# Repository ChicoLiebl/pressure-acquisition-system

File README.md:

# pressure-acquisition-system

Acquisition system for a piezoelectric pressure sensor, model 601A from Kistler. This system was developed as my electrical engineering graduation project.

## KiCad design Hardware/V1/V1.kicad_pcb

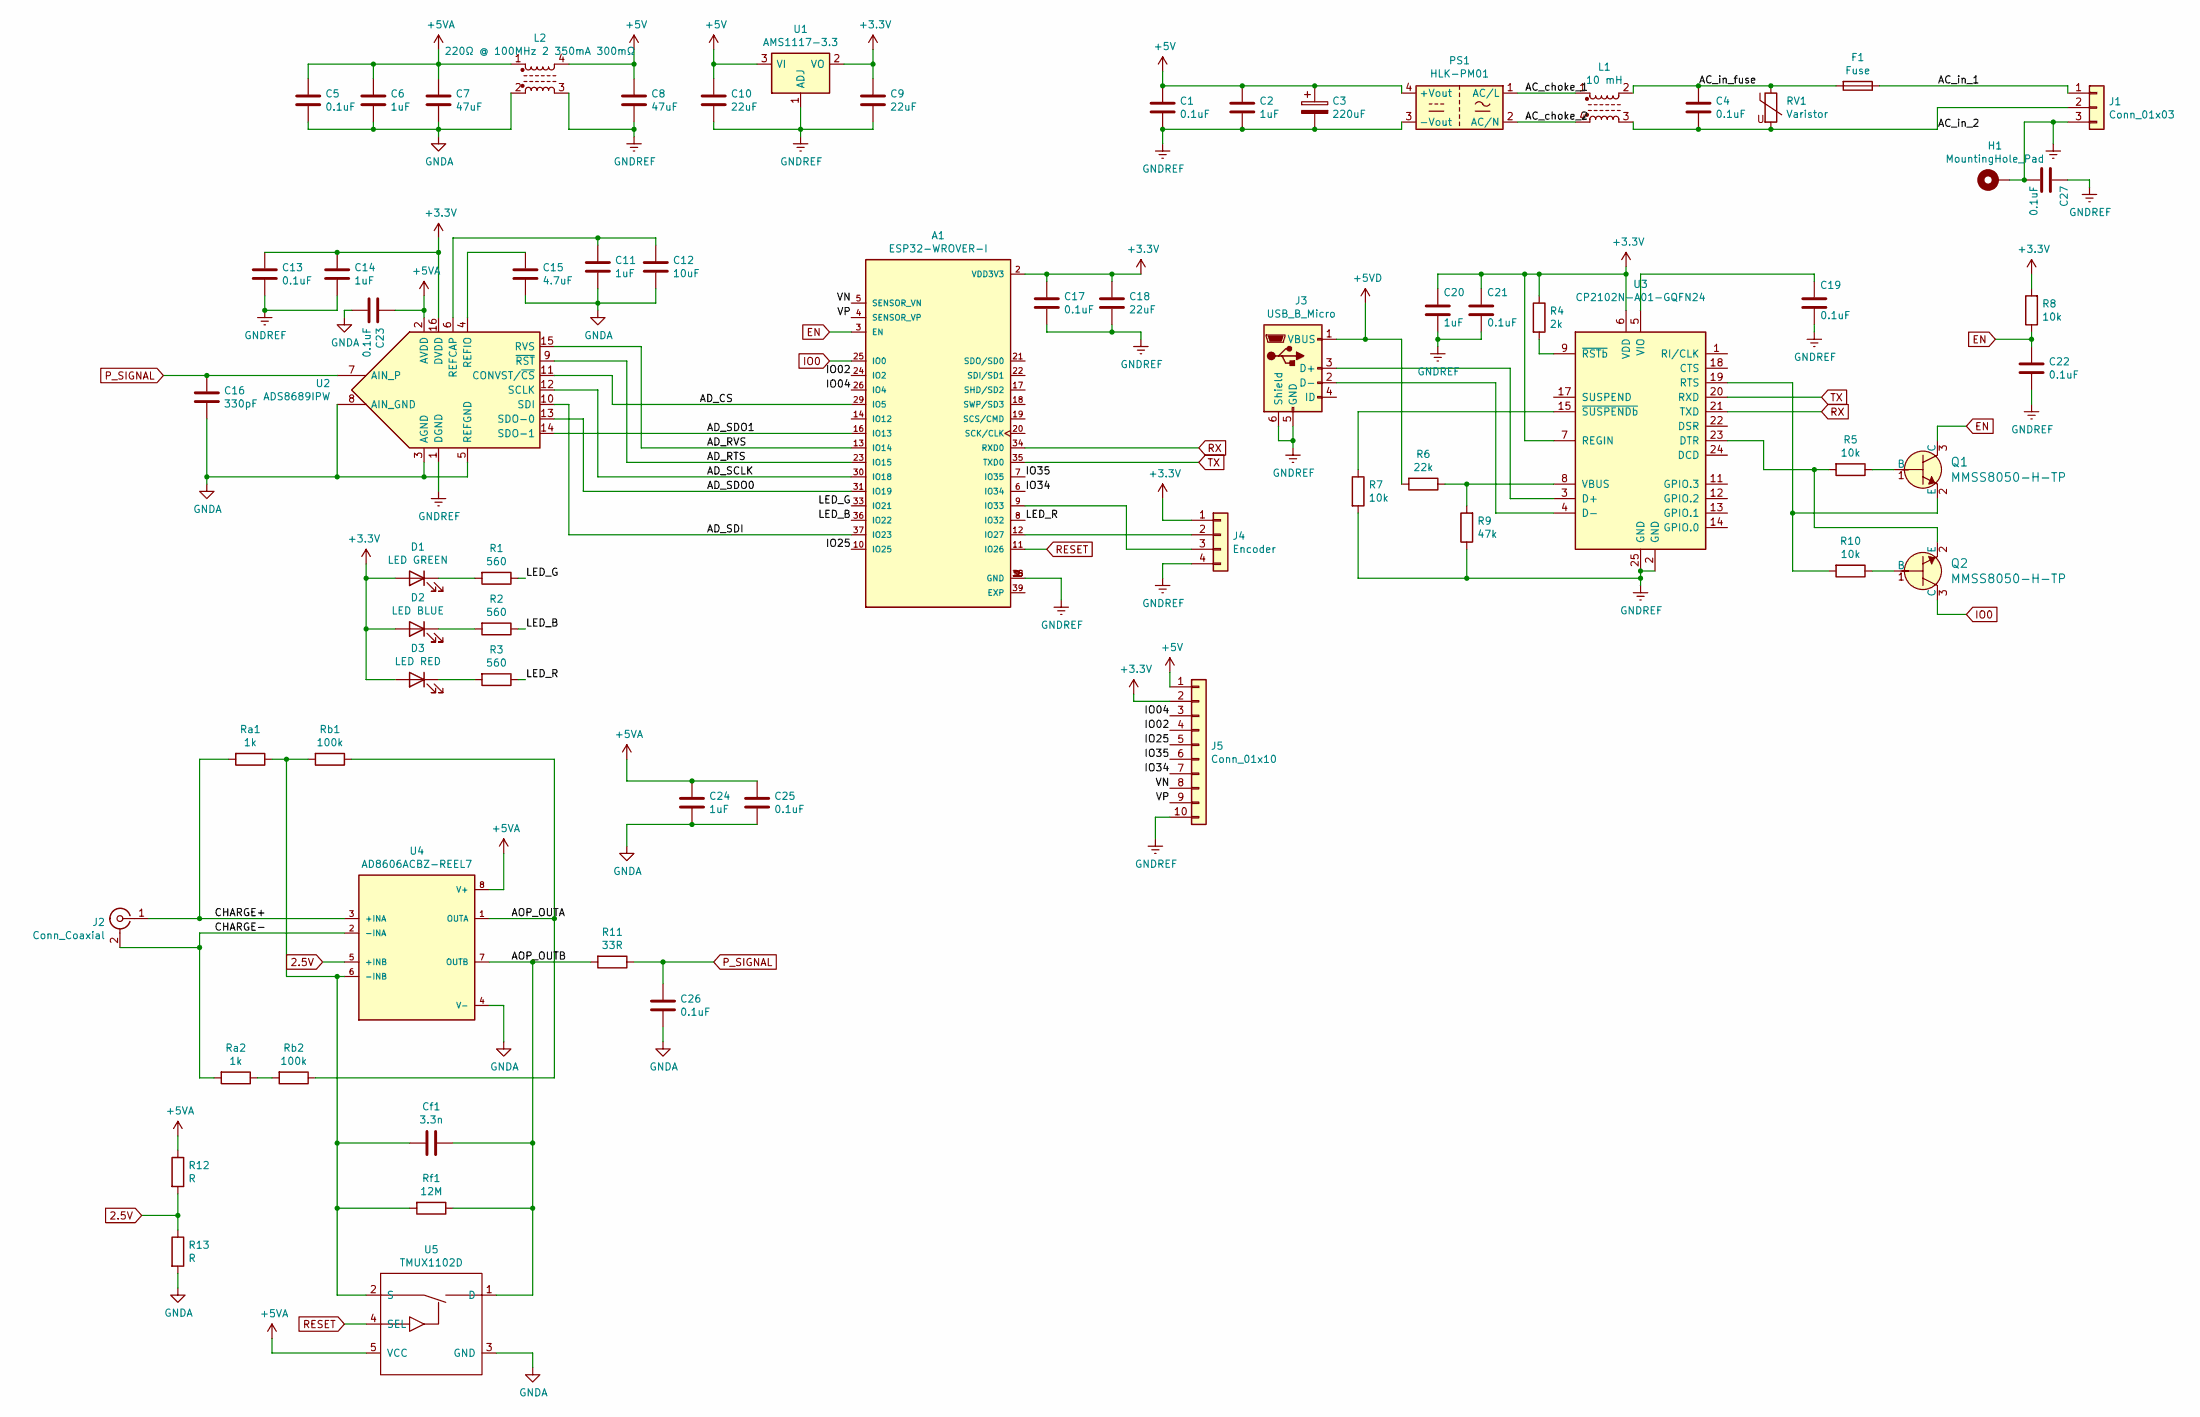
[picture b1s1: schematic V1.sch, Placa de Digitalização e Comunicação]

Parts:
A1: ESP32-WROVER-I; XCVR_ESP32-WROVER-I; DIGI-KEY_PART_NUMBER 1904-1008-1-ND
C1, C5, C13, C17, C19, C21, C22, C23, C25, C26, C27: 0.1uF; 0603
C2, C6, C11, C14, C20, C24: 1uF; 0805
C3: 220uF; CP_Radial_D10.0mm_P2.50mm
C4: 0.1uF; C_Rect_L9.0mm_W3.8mm_P7.50mm_MKT
C7, C8: 47uF; 1206
C9, C10, C18: 22uF; 0805
C12: 10uF; 0805
C15: 4.7uF; 0805
C16: 330pF; 0603
Cf1: 3.3n; 0603
D1: LED GREEN; 0603
D2: LED BLUE; 0603
D3: LED RED; 0603
F1: Fuse; Fuse_BelFuse_0ZRE0025FF_L9.6mm_W3.8mm
H1: MountingHole_Pad; MountingHole_2.2mm_M2_DIN965_Pad
J1: Conn_01x03; AC-Input
J2: Conn_Coaxial; BNC_Header
J3: USB_B_Micro; USB_Micro-AB_Molex_47590-0001
J4: Encoder; PinHeader_1x04_P1.27mm_Vertical
J5: Conn_01x10; PinHeader_1x10_P2.54mm_Vertical
L1: 10 mH; UU9.8
L2: 220Ω @ 100MHz 2 350mA 300mΩ; ACM3225-2P
PS1: HLK-PM01; Converter_ACDC_HiLink_HLK-PMxx
Q1, Q2: MMSS8050-H-TP; SOT-23-3; MPN MMSS8050-H-TP; Digi-Key_PN MMSS8050-H-TPMSCT-ND
R1, R2, R3: 560; 0603
R4: 2k; 0603
R5, R7, R8, R10: 10k; 0603
R6: 22k; 0603
R9: 47k; 0603
R11: 33R; 0603
R12, R13: R; 0603
RV1: Varistor; RV_Disc_D12mm_W3.9mm_P7.5mm
Ra1, Ra2: 1k; 0603
Rb1, Rb2: 100k; 0603
Rf1: 12M; 0603
U1: AMS1117-3.3; SOT-223-3_TabPin2
U2: ADS8689IPW; TSSOP-16_4.4x5mm_P0.65mm
U3: CP2102N-A01-GQFN24; QFN-24-1EP_4x4mm_P0.5mm_EP2.6x2.6mm
U4: AD8606ACBZ-REEL7; SOIC-8_3.9x4.9mm_P1.27mm; PARTREV O
U5: TMUX1102D; SOT-23-5_HandSoldering

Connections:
2.5V: R12.2, R13.1, U4.5 (+INB)
+3V3: A1.2 (VDD3V3), C9.1, C13.1, C14.1, C17.1, C18.1, C20.1, C21.1, D1.2 (A), D2.2 (A), D3.2 (A), J4.1, J5.2, R4.1, R8.2, U1.2 (VO), U2.16 (DVDD), U3.6 (VDD), U3.7 (REGIN)
+5V: C1.1, C2.1, C3.1, C8.1, C10.1, J5.1, L2.4, PS1.4 (+Vout), U1.3 (VI)
+5VA: C5.1, C6.1, C7.1, C23.1, C24.1, C25.1, L2.1, R12.1, U2.2 (AVDD), U4.8 (V+), U5.5 (VCC)
+5VD: J3.1 (VBUS), R6.2
/AC_choke_1: L1.1, PS1.1 (AC/L)
/AC_choke_2: L1.4, PS1.2 (AC/N)
/AC_in_1: F1.1, J1.1
/AC_in_2: C4.2, J1.2, L1.3, RV1.2
/AC_in_fuse: C4.1, F1.2, L1.2, RV1.1
/AD_CS: A1.29 (IO5), U2.11 (CONVST/~CS)
/AD_RTS: A1.23 (IO15), U2.9 (~RST)
/AD_RVS: A1.13 (IO14), U2.15 (RVS)
/AD_SCLK: A1.30 (IO18), U2.12 (SCLK)
/AD_SDI: A1.37 (IO23), U2.10 (SDI)
/AD_SDO0: A1.31 (IO19), U2.13 (SDO-0)
/AD_SDO1: A1.16 (IO13), U2.14 (SDO-1)
/AOP_OUTA: Rb1.1, Rb2.1, U4.1 (OUTA)
/AOP_OUTB: Cf1.1, R11.2, Rf1.1, U4.7 (OUTB), U5.1 (D)
/CHARGE+: J2.1 (In), Ra1.2, U4.3 (+INA)
/CHARGE-: J2.2 (Ext), Ra2.2, U4.2 (-INA)
/IO02: A1.24 (IO2), J5.4
/IO04: A1.26 (IO4), J5.3
/IO25: A1.10 (IO25), J5.5
/IO34: A1.6 (IO34), J5.7
/IO35: A1.7 (IO35), J5.6
/LED_B: A1.36 (IO22), R2.1
/LED_G: A1.33 (IO21), R1.1
/LED_R: A1.8 (IO32), R3.1
/VN: A1.5 (SENSOR_VN), J5.8
/VP: A1.4 (SENSOR_VP), J5.9
EN: A1.3 (EN), C22.1, Q1.3 (C), R8.1
Earth: C27.2, H1.1, J1.3
GNDA: C5.2, C6.2, C7.2, C11.2, C12.2, C15.2, C16.2, C23.2, C24.2, C25.2, C26.2, L2.2, R13.2, U2.3 (AGND), U2.5 (REFGND), U2.8 (AIN_GND), U4.4 (V-), U5.3 (GND)
GNDREF: A1.1 (GND), A1.15 (GND), A1.38 (GND), C1.2, C2.2, C3.2, C8.2, C9.2, C10.2, C13.2, C14.2, C17.2, C18.2, C19.2, C20.2, C21.2, C22.2, C27.1, J3.5 (GND), J3.6 (Shield), J4.4, J5.10, L2.3, PS1.3 (-Vout), R7.2, R9.1, U1.1 (ADJ), U2.1 (DGND), U3.2 (GND), U3.25 (GND)
IO0: A1.25 (IO0), Q2.3 (C)
unnamed: A1.9 (IO33), J4.3
unnamed: A1.12 (IO27), J4.2
unnamed: C11.1, C12.1, U2.6 (REFCAP)
unnamed: C15.1, U2.4 (REFIO)
unnamed: C19.1, U3.5 (VIO)
unnamed: Cf1.2, Ra1.1, Rb1.2, Rf1.2, U4.6 (-INB), U5.2 (S)
unnamed: D1.1 (K), R1.2
unnamed: D2.1 (K), R2.2
unnamed: D3.1 (K), R3.2
unnamed: J3.2 (D-), U3.4 (D-)
unnamed: J3.3 (D+), U3.3 (D+)
unnamed: Q1.1 (B), R5.1
unnamed: Q1.2 (E), R10.2, U3.19 (RTS)
unnamed: Q2.1 (B), R10.1
unnamed: Q2.2 (E), R5.2, U3.23 (DTR)
unnamed: R4.2, U3.9 (~RSTb)
unnamed: R6.1, R9.2, U3.8 (VBUS)
unnamed: R7.1, U3.15 (~SUSPENDb)
unnamed: Ra2.1, Rb2.2
P_SIGNAL: C16.1, C26.1, R11.1, U2.7 (AIN_P)
RESET: A1.11 (IO26), U5.4 (SEL)
RX: A1.34 (RXD0), U3.21 (TXD)
TX: A1.35 (TXD0), U3.20 (RXD)

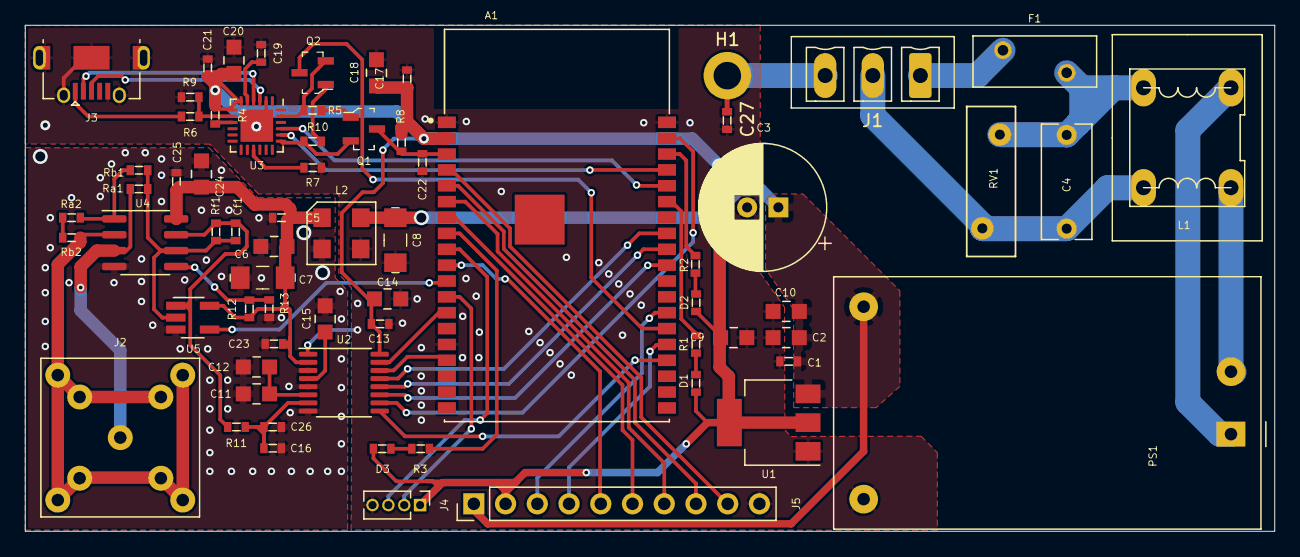
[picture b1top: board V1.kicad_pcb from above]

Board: 2 copper layers, 100.0 x 40.5 mm, 68 parts (0 on the bottom side), 59 nets.

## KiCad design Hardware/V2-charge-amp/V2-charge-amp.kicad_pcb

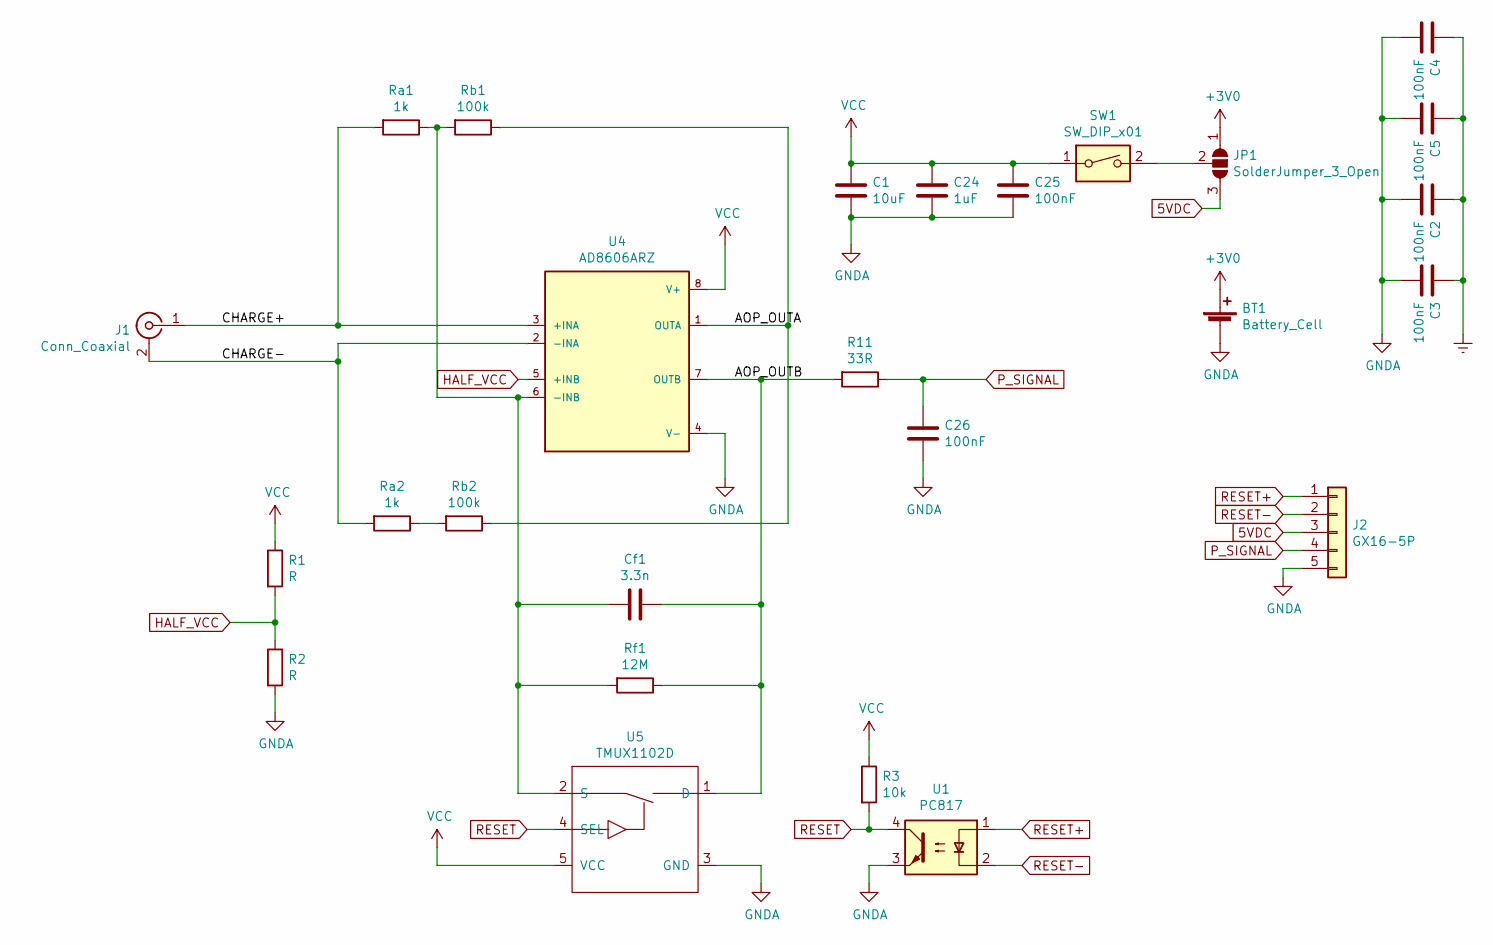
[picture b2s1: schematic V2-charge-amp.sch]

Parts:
BT1: Battery_Cell; PinHeader_1x02_P2.54mm_Vertical
C1: 10uF; 0805
C2, C3, C4, C5, C25, C26: 100nF; 0603
C24: 1uF; 0805
Cf1: 3.3n; 0603
J1: Conn_Coaxial; BNC_Header
J2: GX16-5P
JP1: SolderJumper_3_Open; SolderJumper-3_P1.3mm_Open_RoundedPad1.0x1.5mm
R1, R2: R; 0603
R3: 10k; 0603
R11: 33R; 0603
Ra1, Ra2: 1k; 0603
Rb1, Rb2: 100k; 0603
Rf1: 12M; 0603
SW1: SW_DIP_x01; PinHeader_1x02_P2.54mm_Vertical
U1: PC817
U4: AD8606ARZ; SOIC-8_3.9x4.9mm_P1.27mm; PARTREV O
U5: TMUX1102D; SOT-23-5_HandSoldering

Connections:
5VDC: J2.3, JP1.3 (B)
+3V0: BT1.1 (+), JP1.1 (A)
/AOP_OUTA: Rb1.1, Rb2.1, U4.1 (OUTA)
/AOP_OUTB: Cf1.1, R11.2, Rf1.1, U4.7 (OUTB), U5.1 (D)
/CHARGE+: J1.1 (In), Ra1.2, U4.3 (+INA)
/CHARGE-: J1.2 (Ext), Ra2.2, U4.2 (-INA)
Earth: C2.1, C3.1, C4.1, C5.1
GNDA: BT1.2 (-), C1.2, C2.2, C3.2, C4.2, C5.2, C24.2, C25.2, C26.2, J2.5, R2.2, U1.3, U4.4 (V-), U5.3 (GND)
HALF_VCC: R1.2, R2.1, U4.5 (+INB)
unnamed: Cf1.2, Ra1.1, Rb1.2, Rf1.2, U4.6 (-INB), U5.2 (S)
unnamed: JP1.2 (C), SW1.2
unnamed: Ra2.1, Rb2.2
P_SIGNAL: C26.1, J2.4, R11.1
RESET: R3.2, U1.4, U5.4 (SEL)
RESET+: J2.1, U1.1
RESET-: J2.2, U1.2
VCC: C1.1, C24.1, C25.1, R1.1, R3.1, SW1.1, U4.8 (V+), U5.5 (VCC)

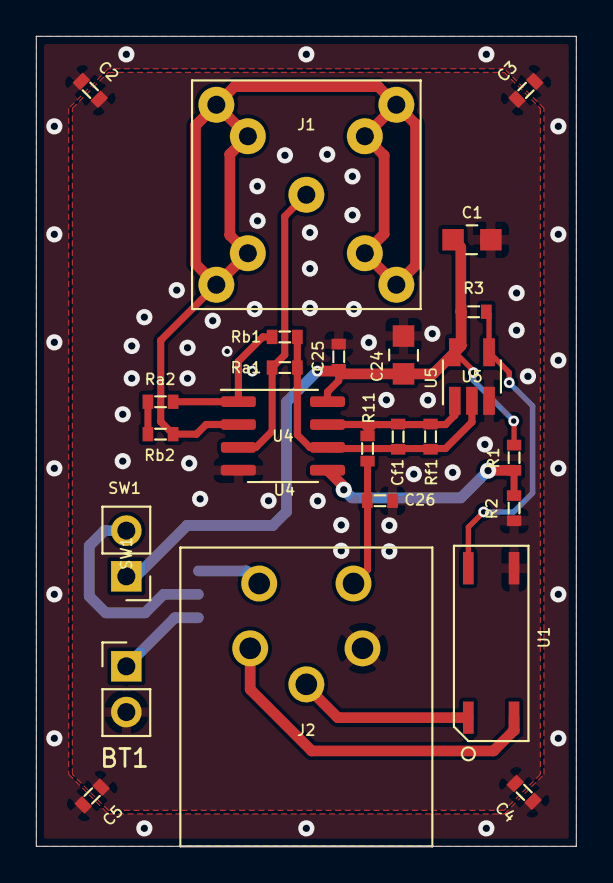
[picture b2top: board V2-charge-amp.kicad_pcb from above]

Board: 4 copper layers, 30.0 x 45.0 mm, 26 parts (1 on the bottom side), 17 nets.

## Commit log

2021-12-02 added pcb first revision
2021-12-03 added specific libs
2021-12-03 fixed paths and updated name
2021-12-03 fixed dk parts submodule
2021-12-03 fix submodule
2021-12-04 changed 100n to 0.1u
2021-12-04 added first firmware code
2021-12-21 changed udp to tcp socket
2021-12-21 finished tcp socket routine
2021-12-21 fixed code
2021-12-21 updated script
2022-01-08 added more wifi networks
2022-01-08 added software requirements
2022-01-10 added tcp client class
2022-01-11 finished TCP client
2022-01-15 added cahce libs
2022-01-29 added software first version
2022-01-29 added integrit test task
2022-03-06 added docs
2022-03-06 added ads8689 component updated RTOS freq to 1kHz
2022-03-10 updated spi code
2022-03-12 using esp_timer_task
2022-03-13 implemented hardware timer
2022-03-26 before using stream buffer
2022-03-27 implemented trigger function
2022-03-28 updated trigger algorithm and UI
2022-04-10 added ble conf and protobuf
2022-04-10 updated layout
2022-04-15 added ble config to software
2022-04-16 finished configration and added fft plot
2022-05-25 Fixed reset GPIO
2022-05-25 removed unused file
